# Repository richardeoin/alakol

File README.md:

# _Alakol_

The non-uniform stress / strain accross a balloon's surface is of interest
for superpressure balloon design. Additionally the technique of
"pre-stretching" can be used to modify the balloon's surface stress
distribution.

**Example plot of stress in a mylar balloon shape, before pre-stretching**

However the understanding of this process, especially for the [mylar
balloon][mylar-balloon] shape popular among amateurs for its simplicity,
has not developed much beyond alchemy. At least in part this is due to a
lack of data and repeatable experiments, and difficulties in controlling
external variables given that some experiments last for 10s of hours.

_Alakol_ is a specialised datalogger for collecting data about the
pre-stretching process. It measures:

- **Gauge pressure** the difference in pressure between inside the balloon
  envelope and outside
- **Ambient temperature** using a K-Type thermocouple
- **Absolute ambient pressure** which can be used to remove any effect
  from ambient pressure changing over time
- **Board Temperature** used as the cold-junction temperature for the
  thermocouple and also useful for calibrating the gauge pressure
  measurement against temperature

The _Alakol_ re-uses the mechanical elements from an Omron M2 Blood
Pressure Monitor (BPM). It can pump ambient air into a +ve pressure up to
~40kPa at a (roughly) constant rate, and then release this pressure via a
solenoid controlled valve. This is not the first superpressure balloon
project to re-use the Omron M2 BPM (was this Leo?) but it takes the
additional step of building a datalogger around it.

🚧🚧🚧🚧
WARNING: The Omron M2 Blood Pressure Monitor is a consumer medical device,
but after the modifications described here it is **no longer suitable for
its original purpose** nor should it be used on people (or anything alive
really). Before modifying an Omron M2 you must ensure it is surpless to any
medical requirements, and that it is clearly marked as non-medical. After
modification the original display panel will no longer fit, which ensures
the extent of the modification is abundantly clear to anyone. The Ormon M2
can usually be purchased off the shelf at consumer stores.
🚧🚧🚧🚧🚧

Project Goals:

- Measure all of the obvious enviromental variables.
- Be pleasant to use.

Not a Goal:

- Be very low cost.

### Hardware

The hardware is a 1.6mm thick 4-layer PCB that replaces all of the internal
PCBs in the M2, except from the motor / value breakout PCB (which has no
components anyhow).

The hardware is designed in KiCad. See the [hardware](hardware/) directory.

### Firmware

The firmware runs on a STM32 microcontroller, and is written in Rust. See
the [firmware](firmware/) directory.

A small [OLED display][adafruit-938] displays measurements, and a very
simple user interfaces allows you to cycle between screens, control the
motor and valve, and zero the gauge pressure reading.

Over Ethernet, it offers a HTTP server for commanding the motor and valve,
whilst a separate TCP server on port 8080 streams the measurement data at a
10Hz update rate.

### Data Analysis

There are some python scripts. See the [software](software/) directory.

### License

See each section (hardware/firmware/software).

[mylar-balloon]: https://www.wikipedia.org/wiki/Mylar_balloon_(geometry)
[adafruit-938]: https://www.adafruit.com/product/938

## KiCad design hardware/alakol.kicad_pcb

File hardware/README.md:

# _Alakol_ hardware
## Replacement control board for the Omron M2

---

## Hardware Overview

* Omron 2SMPP-02 gauge pressure sensor
  * Resistive wheatstone bridge
  * TI REF3325 + LTC2064 to provide constant current source
  * AD8226 In-Amp
* MS5607 Sensor
  * Ambient Pressure
  * Board Temperature (close to 2SMPP-02)
* K-Type Thermocouple (Al/Ch)
  * AD8226 In-Amp
* Microcontroller
  * STM32H743VIT6
  * KSZ8081RN Ethernet PHY
* DC Power Jack
  * Centre +ve
  * 4.6V - 18V
  * Or 4xAA batteries!
* Fits in existing Omron M2 housing
  * Dimensions: 78.0mm x 56.0mm (3.07" x 2.20")

| | |
| --- | --- |
| Schematic | [svg](output/schematic/svg/alakol.svg)/[pdf](output/schematic/pdf/alakol.pdf)
| BOM | [csv](output/bom/bom.csv)
| Layout | [svg](output/layout/svg)/[pdf](output/layout/pdf)/[dxf](output/layout/dxf)
| Gerbers | [gerbers](output/layout/gerber)

---

## License

Hardware is licensed under CERN OHL v1.2. See [LICENSE.md](LICENSE.md)

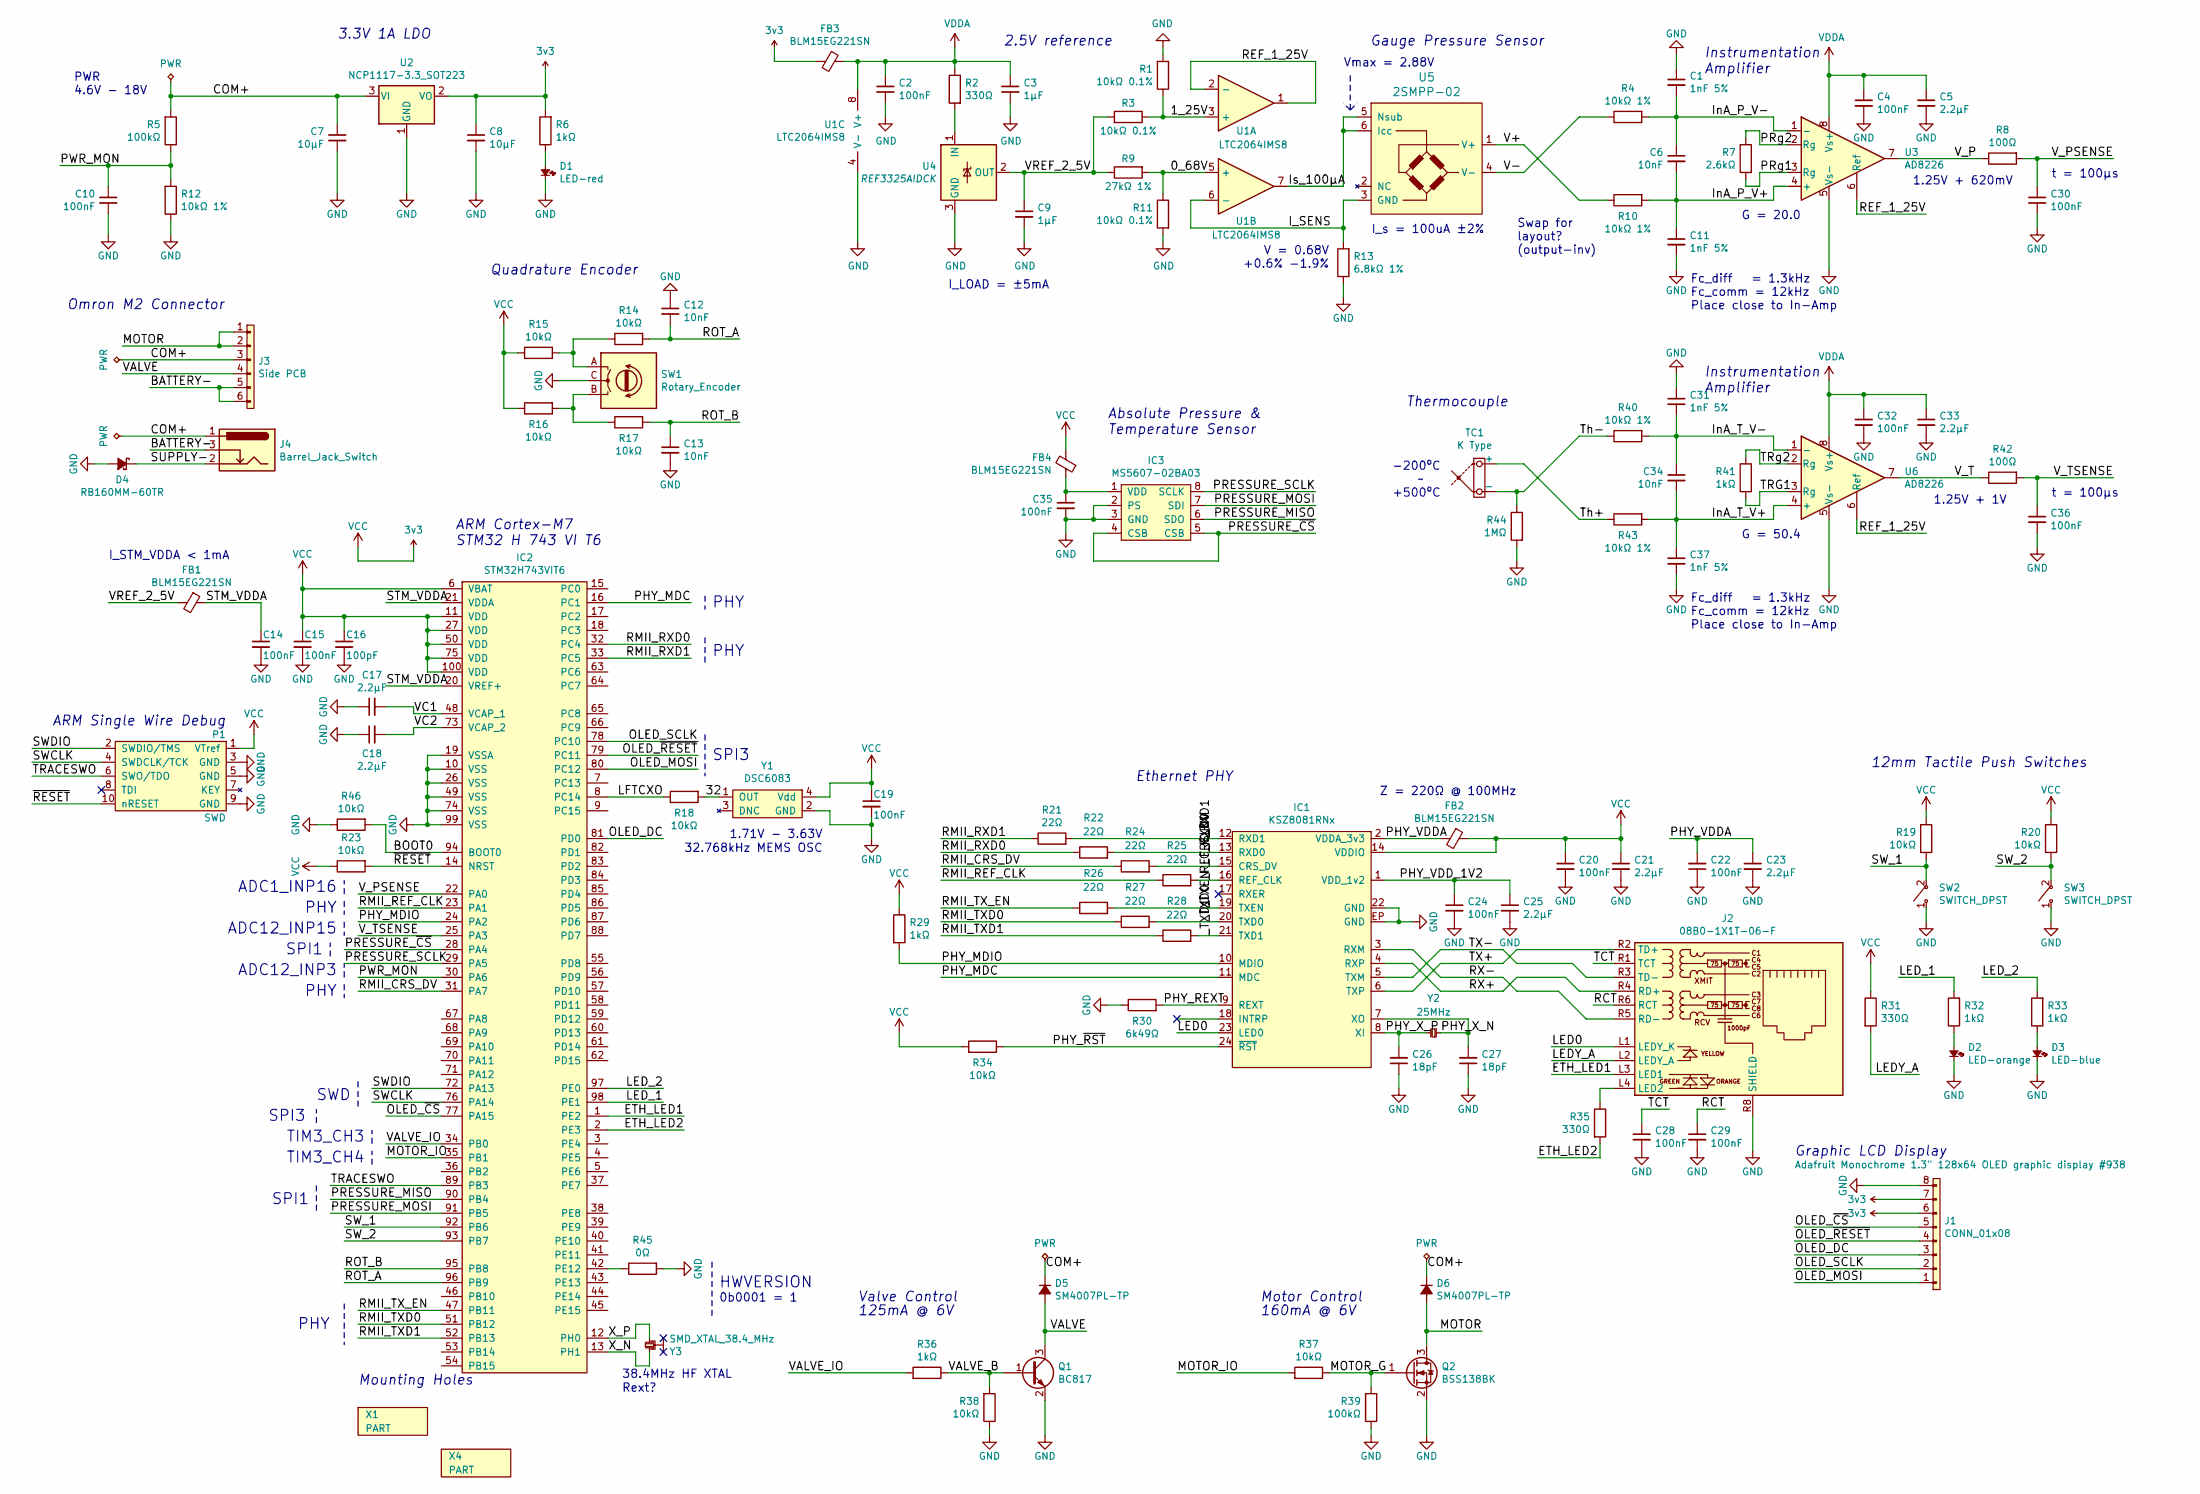
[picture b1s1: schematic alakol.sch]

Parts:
C1, C11, C31, C37: 1nF 5%; 0402
C2, C4, C10, C14, C15, C19, C20, C22, C24, C28, C29, C30, C32, C35, C36: 100nF; 0402
C3, C9: 1µF; 0402
C5, C17, C18, C21, C23, C25, C33: 2.2µF; 0603
C6, C12, C13, C34: 10nF; 0402
C7, C8: 10µF; 0603
C16: 100pF; 0402
C26, C27: 18pF; 0402
D1: LED-red; 0603-LED
D2: LED-orange; 0603-LED
D3: LED-blue; 0603-LED
D4: RB160MM-60TR; D_SOD-123; Farnell 2673070
D5, D6: SM4007PL-TP; D_SOD-123F; Digikey SM4007PL-TPMSCT-ND
FB1, FB2, FB3, FB4: BLM15EG221SN; 0402; Digikey 490-4005-1-ND
IC1: KSZ8081RNx; QFN-24-EP-MICREL; Farnell 2509802
IC2: STM32H743VIT6; LQFP-100; Farnell 2820776
IC3: MS5607-02BA03; MS5611; Digikey 223-1198-1-ND
J1: CONN_01x08; SIL-254P-08; Digikey 1528-1512-ND
J2: 08B0-1X1T-06-F; Digikey 507-1445-ND
J3: Side PCB; Omron_Playbook_Footprint
J4: Barrel_Jack_Switch; BarrelJack_CUI_PJ-102AH_Horizontal
P1: SWD; FTSH-105-01-L-DV-K-ANCHOR; Farnell 2856879
Q1: BC817; SOT-23; Digikey 1727-2919-1-ND
Q2: BSS138BK; SOT-23; Digikey BSS138BK,215
R1, R3, R11: 10kΩ 0.1%; 0402
R2, R31, R35: 330Ω; 0402
R4, R10, R12, R40, R43: 10kΩ 1%; 0402
R5, R39: 100kΩ; 0402
R6, R29, R32, R33, R36, R41: 1kΩ; 0402
R7: 2.6kΩ; 0402
R8, R42: 100Ω; 0402
R9: 27kΩ 1%; 0402
R13: 6.8kΩ 1%; 0402
R14, R15, R16, R17, R18, R19, R20, R23, R34, R37, R38, R46: 10kΩ; 0402
R21, R22, R24, R25, R26, R27, R28: 22Ω; 0402
R30: 6k49Ω; 0402; Farnell 1469727
R44: 1MΩ; 0402
R45: 0Ω; 0402
SW1: Rotary_Encoder; PEC11R-4xxxF-Nxxxx; Digikey PEC11R-4215F-N0024-ND
SW2, SW3: SWITCH_DPST; SW_PUSH-12mm-OMRON_4xxx_5xxx; Part Omron B3F-4000; Digikey SW411-ND
TC1: K Type; PCC-SMP; Digikey 1568-1306-ND
U1: LTC2064IMS8; MSOP-8; Digikey LTC2064IMS8#PBF-ND
U2: NCP1117-3.3_SOT223; SOT-223-3_TabPin2; Digikey NCP1117ST33T3GOSCT-ND
U3, U6: AD8226; MSOP-8; Digikey AD8226ARMZ-ND
U4: REF3325AIDCK; SOT-323; Digikey 296-39164-1-ND
U5: 2SMPP-02; Farnell 2113270
X1, X4: PART; drill
Y1: DSC6083; XTAL-32x25-CDFN4; Digikey DSC6083CI2A-032K768-ND
Y2: 25MHz; XTAL-50x32; Digikey 535-10645-1-ND
Y3: SMD_XTAL_38.4_MHz; XTAL-25x20; Farnell 2849405

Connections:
3v3: C8.1, C15.1, C16.1, C19.1, C20.1, C21.1, FB2.1, FB3.2, FB4.2, IC1.14 (VDDIO), IC2.6 (VBAT), IC2.11 (VDD), IC2.27 (VDD), IC2.50 (VDD), IC2.75 (VDD), IC2.100 (VDD), J1.6, J1.7, P1.1 (VTref), R6.2, R15.1, R16.1, R19.2, R20.2, R23.1, R29.1, R31.1, R34.2, U2.2 (VO), Y1.4 (Vdd)
/0_68V: R9.2, R11.1, U1.5 (+)
/1_25V: R1.1, R3.1, U1.3 (+)
/32: R18.2, Y1.1 (OUT)
/BATTERY-: J3.5, J3.6, J4.3
/BOOT0: IC2.94 (BOOT0), R46.2
/COM+: C7.1, D5.1 (K), D6.1 (K), J3.3, J4.1, R5.2, U2.3 (VI)
/ETH_LED1: IC2.1 (PE2), J2.L3 (LED1)
/ETH_LED2: IC2.2 (PE3), R35.2
/I_SENS: R13.2, U1.6 (-), U5.3 (GND)
/InA_P_V+: C6.2, C11.1, R10.2, U3.4 (+)
/InA_P_V-: C1.2, C6.1, R4.2, U3.1 (-)
/InA_T_V+: C34.2, C37.1, R43.2, U6.4 (+)
/InA_T_V-: C31.2, C34.1, R40.2, U6.1 (-)
/Is_100µA: U1.7, U5.5 (Nsub), U5.6 (Icc)
/LED0: IC1.23 (LED0), J2.L1 (LEDY_K)
/LEDY_A: J2.L2 (LEDY_A), R31.2
/LED_1: IC2.98 (PE1), R32.2
/LED_2: IC2.97 (PE0), R33.2
/LFTCXO: IC2.8 (PC14), R18.1
/MOTOR: D6.2 (A), J3.1, J3.2, Q2.3 (D)
/MOTOR_G: Q2.1 (G), R37.1, R39.2
/MOTOR_IO: IC2.35 (PB1), R37.2
/OLED_DC: IC2.81 (PD0), J1.3
/OLED_MOSI: IC2.80 (PC12), J1.1
/OLED_SCLK: IC2.78 (PC10), J1.2
/OLED_~CS~: IC2.77 (PA15), J1.5
/OLED_~RESET~: IC2.79 (PC11), J1.4
/PHY_MDC: IC1.11 (MDC), IC2.16 (PC1)
/PHY_MDIO: IC1.10 (MDIO), IC2.24 (PA2), R29.2
/PHY_REXT: IC1.9 (REXT), R30.2
/PHY_VDDA: C22.2, C23.1, FB2.2, IC1.2 (VDDA_3v3)
/PHY_VDD_1V2: C24.1, C25.1, IC1.1 (VDD_1v2)
/PHY_X_N: C27.2, IC1.7 (XO), Y2.1
/PHY_X_P: C26.2, IC1.8 (XI), Y2.2
/PHY_~RST~: IC1.24 (~RST), R34.1
/PRESSURE_MISO: IC2.90 (PB4), IC3.6 (SDO)
/PRESSURE_MOSI: IC2.91 (PB5), IC3.7 (SDI)
/PRESSURE_SCLK: IC2.29 (PA5), IC3.8 (SCLK)
/PRESSURE_~CS~: IC2.28 (PA4), IC3.4 (CSB), IC3.5 (CSB)
/PRg1: R7.2, U3.3 (Rg)
/PRg2: R7.1, U3.2 (Rg)
/PWR_MON: C10.1, IC2.30 (PA6), R5.1, R12.2
/RCT: C29.1, J2.R6 (RCT)
/REF_1_25V: U1.1, U1.2 (-), U3.6 (Ref), U6.6 (Ref)
/RMII_CRS_DV: IC2.31 (PA7), R24.1
/RMII_REF_CLK: IC2.23 (PA1), R25.1
/RMII_RXD0: IC2.32 (PC4), R22.1
/RMII_RXD1: IC2.33 (PC5), R21.1
/RMII_TXD0: IC2.51 (PB12), R27.1
/RMII_TXD1: IC2.52 (PB13), R28.1
/RMII_TX_EN: IC2.47 (PB11), R26.1
/ROT_A: C12.2, IC2.96 (PB9), R14.2
/ROT_B: C13.1, IC2.95 (PB8), R17.2
/RX+: IC1.4 (RXP), J2.R4 (RD+)
/RX-: IC1.3 (RXM), J2.R5 (RD-)
/STM_VDDA: C14.1, FB1.1, IC2.20 (VREF+), IC2.21 (VDDA)
/SUPPLY-: D4.1 (K), J4.2
/SWCLK: IC2.76 (PA14), P1.4 (SWDCLK/TCK)
/SWDIO: IC2.72 (PA13), P1.2 (SWDIO/TMS)
/SW_1: IC2.92 (PB6), R19.1, SW2.2
/SW_2: IC2.93 (PB7), R20.1, SW3.2
/TCT: C28.1, J2.R1 (TCT)
/TRACESWO: IC2.89 (PB3), P1.6 (SWO/TDO)
/TRG1: R41.2, U6.3 (Rg)
/TRg2: R41.1, U6.2 (Rg)
/TX+: IC1.6 (TXP), J2.R2 (TD+)
/TX-: IC1.5 (TXM), J2.R3 (TD-)
/Th+: R43.1, TC1.1 (+)
/Th-: R40.1, R44.1, TC1.2 (-)
/V+: R10.1, U5.1 (V+)
/V-: R4.1, U5.4 (V-)
/VALVE: D5.2 (A), J3.4, Q1.3 (C)
/VALVE_B: Q1.1 (B), R36.1, R38.2
/VALVE_IO: IC2.34 (PB0), R36.2
/VC1: C17.2, IC2.48 (VCAP_1)
/VC2: C18.2, IC2.73 (VCAP_2)
/VREF_2_5V: C9.1, FB1.2, R3.2, R9.1, U4.2 (OUT)
/V_P: R8.1, U3.7
/V_PSENSE: C30.1, IC2.22 (PA0), R8.2
/V_T: R42.1, U6.7
/V_TSENSE: C36.1, IC2.25 (PA3), R42.2
/X_N: IC2.13 (PH1), Y3.3
/X_P: IC2.12 (PH0), Y3.1
/_CRS_DV: IC1.15 (CRS_DV), R24.2
/_REF_CLK: IC1.16 (REF_CLK), R25.2
/_RXD0: IC1.13 (RXD0), R22.2
/_RXD1: IC1.12 (RXD1), R21.2
/_TXD0: IC1.20 (TXD0), R27.2
/_TXD1: IC1.21 (TXD1), R28.2
/_TXEN: IC1.19 (TXEN), R26.2
/~RESET: IC2.14 (NRST), P1.10 (nRESET), R23.2
GND: C1.1, C2.2, C3.2, C4.2, C5.2, C7.2, C8.2, C9.2, C10.2, C11.2, C12.1, C13.2, C14.2, C15.2, C16.2, C17.1, C18.1, C19.2, C20.2, C21.2, C22.1, C23.2, C24.2, C25.2, C26.1, C27.1, C28.2, C29.2, C30.2, C31.1, C32.2, C33.2, C35.2, C36.2, C37.2, D1.1, D2.1, D3.1, D4.2 (A), IC1.22 (GND), IC1.EP (GND), IC2.10 (VSS), IC2.19 (VSSA), IC2.26 (VSS), IC2.49 (VSS), IC2.74 (VSS), IC2.99 (VSS), IC3.2 (PS), IC3.3 (GND), J1.8, J2.R8 (SHIELD), P1.3 (GND), P1.5 (GND), P1.9 (GND), Q1.2 (E), Q2.2 (S), R1.2, R11.2, R12.1, R13.1, R30.1, R38.1, R39.1, R44.2, R45.2, R46.1, SW1.C, SW2.1, SW3.1, U1.4 (V-), U2.1 (GND), U3.5 (Vs-), U4.3 (GND), U6.5 (Vs-), Y1.2 (GND)
unnamed: C35.1, FB4.1, IC3.1 (VDD)
unnamed: D1.2, R6.1
unnamed: D2.2, R32.1
unnamed: D3.2, R33.1
unnamed: IC2.42 (PE12), R45.1
unnamed: J2.L4 (LED2), R35.1
unnamed: R2.2, U4.1 (IN)
unnamed: R14.1, R15.2, SW1.A
unnamed: R16.2, R17.1, SW1.B
VDDA: C2.1, C3.1, C4.1, C5.1, C32.1, C33.1, FB3.1, R2.1, U1.8 (V+), U3.8 (Vs+), U6.8 (Vs+)

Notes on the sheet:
ARM Cortex-M7 STM32 H 743 VI T6
ARM Single Wire Debug
38.4MHz HF XTAL
1.71V - 3.63V
Graphic LCD Display
Mounting Holes
32.768kHz MEMS OSC
3.3V 1A LDO
12mm Tactile Push Switches
PWR 4.6V - 18V
Quadrature Encoder
Rext?
PHY
SWD
Ethernet PHY
Gauge Pressure Sensor
G = 20.0
Fc_diff = 1.3kHz Fc_comm = 12kHz Place close to In-Amp
I_s = 100uA ±2%
Instrumentation Amplifier
2.5V reference
1.25V + 620mV
Swap for layout? (output-inv)
Z = 220Ω @ 100MHz
I_STM_VDDA < 1mA
Vmax = 2.88V
V = 0.68V +0.6% -1.9%
Omron M2 Connector
Valve Control
Motor Control
G = 50.4
1.25V + 1V
-200ºC ~~ +500ºC
I_LOAD = ±5mA
t = 100µs
Absolute Pressure & Temperature Sensor
Thermocouple
125mA @ 6V
160mA @ 6V
SPI3

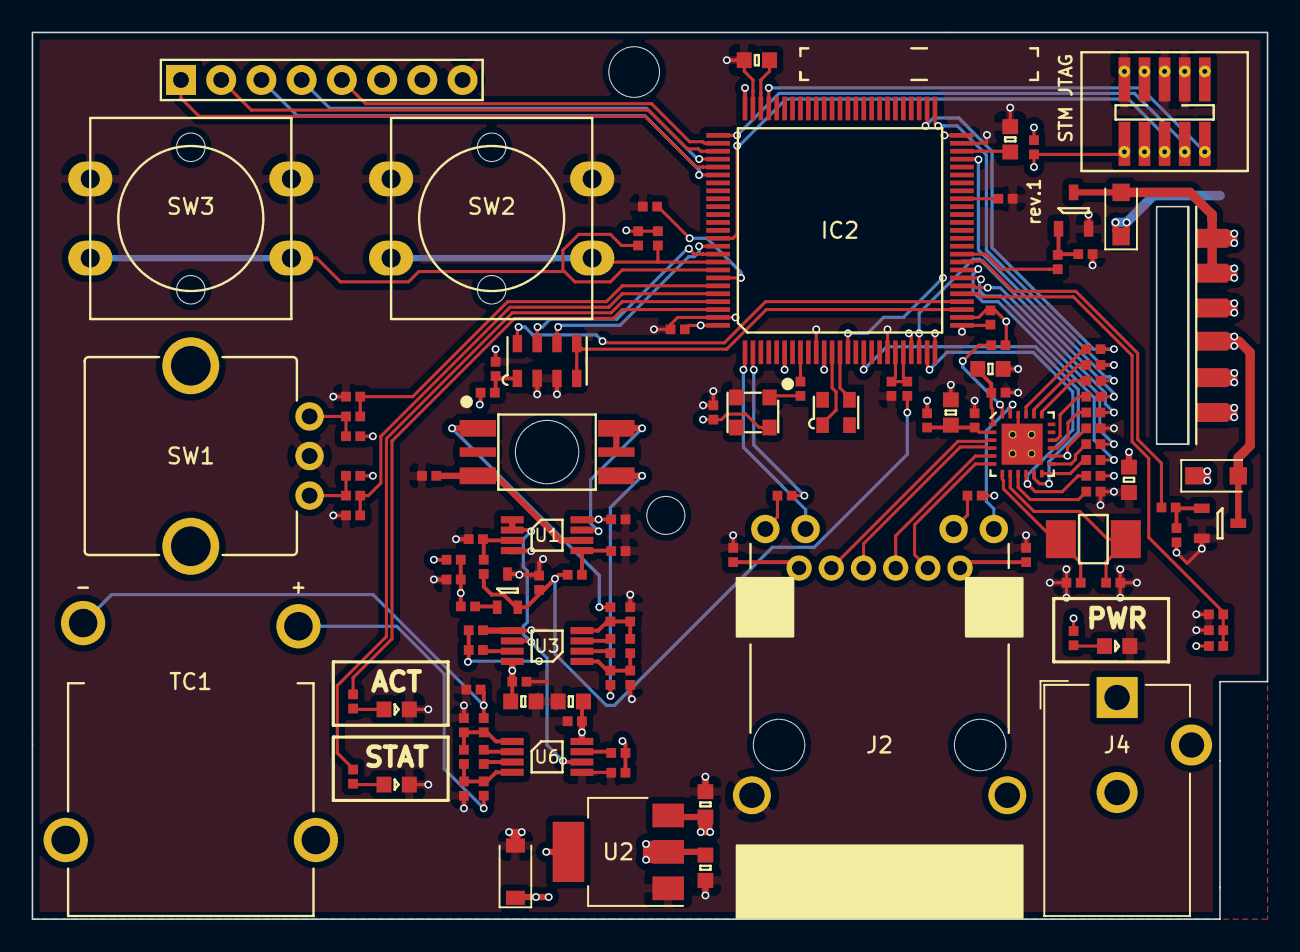
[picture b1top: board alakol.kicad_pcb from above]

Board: 4 copper layers, 78.0 x 56.0 mm, 118 parts (0 on the bottom side), 103 nets.

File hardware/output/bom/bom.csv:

Reference, Quantity, Value, Footprint, Datasheet, Digikey, Farnell, Toby, Module, THT, Part, User Manual
C11 C1 C37 C31 ,4,"1nF 5%","agg:0402",""
C12 C13 C6 C34 ,4,"10nF","agg:0402",""
C15 C10 C19 C24 C20 C22 C28 C29 C4 C2 C14 C32 C36 C30 C35 ,15,"100nF","agg:0402",""
C16 ,1,"100pF","agg:0402",""
C17 C18 C25 C21 C5 C23 C33 ,7,"2.2µF","agg:0603",""
C27 C26 ,2,"18pF","agg:0402",""
C3 C9 ,2,"1µF","agg:0402",""
C8 C7 ,2,"10µF","agg:0603",""
D1 ,1,"LED-red","agg:0603-LED",""
D2 ,1,"LED-orange","agg:0603-LED",""
D3 ,1,"LED-blue","agg:0603-LED",""
D4 ,1,"RB160MM-60TR","Diode_SMD:D_SOD-123","https://www.rohm.com/datasheet/RB160MM-60/rb160mm-60tr-e","","2673070","","","","",""
D5 D6 ,2,"SM4007PL-TP","Diode_SMD:D_SOD-123F","http://www.mccsemi.com/up_pdf/SM4001PL-SM4007PL(SOD-123FL).PDF","SM4007PL-TPMSCT-ND","2295709","","","","",""
FB2 FB1 FB3 FB4 ,4,"BLM15EG221SN","agg:0402","https://www.murata.com/en-us/products/productdata/8796750970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","490-4005-1-ND","","","","","",""
IC1 ,1,"KSZ8081RNx","agg:QFN-24-EP-MICREL","http://ww1.microchip.com/downloads/en/DeviceDoc/KSZ8081RNA_RND.pdf","","2509802","","","","",""
IC2 ,1,"STM32H743VIT6","agg:LQFP-100","http://www.st.com/st-web-ui/static/active/en/resource/techni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","497-17720-ND","2820776","","","","",""
IC3 ,1,"MS5607-02BA03","agg:MS5611","https://www.te.com/commerce/DocumentDelivery/DDEController?A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","223-1198-1-ND","","","","","",""
J1 ,1,"CONN_01x08","agg:SIL-254P-08","","1528-1512-ND","","","Adafruit Monochrome 1.3" 128x64 OLED graphic display #938","true","",""
J2 ,1,"08B0-1X1T-06-F","rem:08B0-1X1T-06-F","https://www.belfuse.com/resources/ICMs/ICMs%20Drawings/08B0-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","507-1445-ND","2675992","","","true","",""
J3 ,1,"Side PCB","rem:Omron_Playbook_Footprint","","","","","","true","",""
J4 ,1,"Barrel_Jack_Switch","Connector_BarrelJack:BarrelJack_CUI_PJ-102AH_Horizontal","https://www.cui.com/product/resource/pj-102ah.pdf","","","","","true","",""
P1 ,1,"SWD","rem:FTSH-105-01-L-DV-K-ANCHOR","","SAM13165CT-ND","2856879","FTSH-105-01-L-DV-K","","","",""
Q1 ,1,"BC817","agg:SOT-23","https://assets.nexperia.com/documents/data-sheet/BC817_SER.pdf","1727-2919-1-ND","","","","","",""
Q2 ,1,"BSS138BK","agg:SOT-23","https://assets.nexperia.com/documents/data-sheet/BSS138BK.pdf","BSS138BK,215","","","","","",""
R11 R3 R1 ,3,"10kΩ 0.1%","agg:0402",""
R12 R4 R10 R40 R43 ,5,"10kΩ 1%","agg:0402",""
R13 ,1,"6.8kΩ 1%","agg:0402",""
R23 R18 R19 R20 R15 R16 R17 R14 R34 R38 R37 R46 ,12,"10kΩ","agg:0402",""
R28 R27 R26 R25 R24 R22 R21 ,7,"22Ω","agg:0402",""
R30 ,1,"6k49Ω","agg:0402","","","1469727","","","","",""
R31 R35 R2 ,3,"330Ω","agg:0402",""
R36 R6 R33 R32 R29 R41 ,6,"1kΩ","agg:0402",""
R44 ,1,"1MΩ","agg:0402",""
R45 ,1,"0Ω","agg:0402",""
R5 R39 ,2,"100kΩ","agg:0402",""
R7 ,1,"2.6kΩ","agg:0402",""
R8 R42 ,2,"100Ω","agg:0402",""
R9 ,1,"27kΩ 1%","agg:0402",""
SW1 ,1,"Rotary_Encoder","rem:PEC11R-4xxxF-Nxxxx","https://www.bourns.com/docs/Product-Datasheets/PEC11R.pdf","PEC11R-4215F-N0024-ND","","","","true","",""
SW2 SW3 ,2,"SWITCH_DPST","rem:SW_PUSH-12mm-OMRON_4xxx_5xxx","https://omronfs.omron.com/en_US/ecb/products/pdf/en-b3f.pdf","SW411-ND","","","","true","Omron B3F-4000",""
TC1 ,1,"K Type","rem:PCC-SMP","https://cdn.sparkfun.com/datasheets/Prototyping/PCC-SMP-K-da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","1568-1306-ND","","","","true","",""
U1 ,1,"LTC2064IMS8","agg:MSOP-8","https://www.analog.com/media/en/technical-documentation/data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","LTC2064IMS8#PBF-ND","","","","","",""
U2 ,1,"NCP1117-3.3_SOT223","Package_TO_SOT_SMD:SOT-223-3_TabPin2","http://www.onsemi.com/pub_link/Collateral/NCP1117-D.PDF","NCP1117ST33T3GOSCT-ND","","","","","",""
U3 U6 ,2,"AD8226","agg:MSOP-8","https://www.analog.com/media/en/technical-documentation/data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","AD8226ARMZ-ND","","","","","",""
U4 ,1,"REF3325AIDCK","agg:SOT-323","http://www.ti.com/lit/ds/symlink/ref3325.pdf","296-39164-1-ND","","","","","",""
U5 ,1,"2SMPP-02","rem:2SMPP-02","https://omronfs.omron.com/en_US/ecb/products/pdf/en-2smpp-02.pdf","Z3059-ND","2113270","","","","","https://omronfs.omron.com/en_US/ecb/products/pdf/en_a282_e1_01.pdf"
X1 X4 ,2,"PART","rem:drill",""
Y1 ,1,"DSC6083","rem:XTAL-32x25-CDFN4","http://ww1.microchip.com/downloads/en/DeviceDoc/DSC60XX-Ultr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","DSC6083CI2A-032K768-ND","","","","","",""
Y2 ,1,"25MHz","agg:XTAL-50x32","https://abracon.com/Resonators/abm3.pdf","535-10645-1-ND","2101328","","","","",""
Y3 ,1,"SMD_XTAL_38.4_MHz","agg:XTAL-25x20","http://www.farnell.com/datasheets/2581416.pdf","535-13191-1-ND","2849405","","","","",""

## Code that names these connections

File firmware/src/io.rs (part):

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
#[cfg(feature = "hardware0")]
pub type PressureSPIPinsT = (
    gpio::gpiob::PB3<Alternate<AF5>>,
    gpio::gpiob::PB4<Alternate<AF5>>,
    gpio::gpiob::PB5<Alternate<AF5>>,
);
#[cfg(not(feature = "hardware0"))]
pub type PressureSPIPinsT = (
    gpio::gpioa::PA5<Alternate<AF5>>,
    gpio::gpiob::PB4<Alternate<AF5>>,
    gpio::gpiob::PB5<Alternate<AF5>>,
);

pub fn gpio_setup(
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    u8,
    (
        // ethernet led
        gpio::gpioe::PE2<Output<PushPull>>,
        gpio::gpioe::PE3<Output<PushPull>>,
    ),
    gpio::gpioe::PE0<Output<PushPull>>, // stat_led
    gpio::gpioe::PE1<Output<PushPull>>, // act_led
    (
        // oled
        gpio::gpioc::PC10<Alternate<AF6>>,
        spi::NoMiso,
        gpio::gpioc::PC12<Alternate<AF6>>,
    ),
    gpio::gpiod::PD0<Output<PushPull>>,
    gpio::gpioc::PC11<Output<PushPull>>,
    gpio::gpioa::PA15<Output<PushPull>>,
    PressureSPIPinsT,
    gpio::gpioa::PA4<Output<PushPull>>, // pressure_cs
    gpio::gpioa::PA0<Analog>,
    gpio::gpioa::PA3<Analog>,
    gpio::gpioa::PA6<Analog>,
    gpio::gpiob::PB0<Output<PushPull>>, // valve_io
    gpio::gpiob::PB1<Alternate<AF2>>,   // motor_io
) {
    // Hardware version
    let h0 = gpioe.pe12.into_pull_up_input();
    let h1 = gpioe.pe13.into_pull_up_input();
    let h2 = gpioe.pe14.into_pull_up_input();
    let h3 = gpioe.pe15.into_pull_up_input();
    let hw = hardware_version(h0, h1, h2, h3).expect("Unknown version");

    // Stat LED
    let stat_led = gpioe.pe0.into_push_pull_output();
    // Act LED
    let act_led = gpioe.pe1.into_push_pull_output();

    // Ethernet LED
    let ethernet_led = (
        gpioe.pe2.into_push_pull_output(),
        gpioe.pe3.into_push_pull_output(),
    );

    // SW
    gpiob.pb6.into_pull_up_input();
    gpiob.pb7.into_pull_up_input();
    gpiob.pb8.into_pull_up_input();
    gpiob.pb9.into_pull_up_input();
    debounce_tick(true);

    // PB3 TRACESWO
    #[cfg(not(feature = "hardware0"))]
    let _traceswo = gpiob.pb3.into_alternate_af0().set_speed(Speed::VeryHigh);

    // Ethernet
    let rmii_ref_clk = gpioa.pa1.into_alternate_af11();
    rmii_ref_clk.set_speed(Speed::VeryHigh);
    let rmii_mdio = gpioa.pa2.into_alternate_af11();
    rmii_mdio.set_speed(Speed::VeryHigh);
    let rmii_mdc = gpioc.pc1.into_alternate_af11();
    rmii_mdc.set_speed(Speed::VeryHigh);
    let rmii_crs_dv = gpioa.pa7.into_alternate_af11();
    rmii_crs_dv.set_speed(Speed::VeryHigh);
    let rmii_rxd0 = gpioc.pc4.into_alternate_af11();
    rmii_rxd0.set_speed(Speed::VeryHigh);
    let rmii_rxd1 = gpioc.pc5.into_alternate_af11();
    rmii_rxd1.set_speed(Speed::VeryHigh);
    let rmii_tx_en = gpiob.pb11.into_alternate_af11();
    rmii_tx_en.set_speed(Speed::VeryHigh);
    let rxii_txd0 = gpiob.pb12.into_alternate_af11();
    rxii_txd0.set_speed(Speed::VeryHigh);
    let rmii_txd1 = gpiob.pb13.into_alternate_af11();
    rmii_txd1.set_speed(Speed::VeryHigh);

    // OLED
    let oled_sck = gpioc.pc10.into_alternate_af6();
    let oled_miso = spi::NoMiso;
    let oled_mosi = gpioc.pc12.into_alternate_af6();
    let oled_spi = (oled_sck, oled_miso, oled_mosi);
    let oled_dc = gpiod.pd0.into_push_pull_output();
    let oled_rst = gpioc.pc11.into_push_pull_output();
    let oled_cs = gpioa.pa15.into_push_pull_output();

    // Pressure sensor
    #[cfg(feature = "hardware0")]
    let pressure_sck = gpiob.pb3.into_alternate_af5();
    #[cfg(not(feature = "hardware0"))]
    let pressure_sck = gpioa.pa5.into_alternate_af5();
    let pressure_miso = gpiob.pb4.into_alternate_af5();
    let pressure_mosi = gpiob.pb5.into_alternate_af5();
    let pressure_spi = (pressure_sck, pressure_miso, pressure_mosi);
    let pressure_cs = gpioa.pa4.into_push_pull_output();

    // ADCs
    let v_psense = gpioa.pa0.into_analog();
    let v_tsense = gpioa.pa3.into_analog();
    let pwr_mon = gpioa.pa6.into_analog();

    // Motors
    let valve_io = gpiob.pb0.into_push_pull_output();
    let motor_io = gpiob.pb1.into_alternate_af2();

    // Hardware
    (
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}

pub fn hardware_version(
    h0: gpio::gpioe::PE12<Input<PullUp>>,
    h1: gpio::gpioe::PE13<Input<PullUp>>,
    h2: gpio::gpioe::PE14<Input<PullUp>>,
    h3: gpio::gpioe::PE15<Input<PullUp>>,
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/// Set state of ethernet LED
pub fn ethernet_led(
    ethernet_led: &mut (
        gpio::gpioe::PE2<Output<PushPull>>,
        gpio::gpioe::PE3<Output<PushPull>>,
    ),
    state: EthernetLED,
) -> Result<(), Never> {
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
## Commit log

2020-04-18 stm32-based hardware for fabriation, rev.0
2020-04-18 Add firmware
2020-04-18 Hardware rev.1
2020-04-18 Add software, with examples and README
2020-04-18 Write a README for the whole project
2020-04-18 Add travis
2020-04-18 Tidy up unused git modules, fix markdown
2020-04-18 Let autoformatter loose on python code
    I don't want to think about formatting
2020-04-18 Add photos, add README for hardware
2020-04-19 Fix units for ms5611 pressure
2020-04-19 Improve READMEs for firmware and software
2020-04-19 Tidy gauge pressure format specifier
2020-04-20 Update photo
2020-04-27 Blank display after 1 hour - it fades after 1000 hours
    See note on Adafruit product page https://www.adafruit.com/product/938
    Switch to representing time with a i64 to avoid the 50 day problem,
    involves some unafe but race is not critical anyhow. And rollover probably
    wasn't an issue either
2020-04-27 Add version and git commit hash to display
2020-04-27 Reduce cold junction temperature offset - needs more investigation
2020-06-23 Bump some dependency versions
2020-11-18 Bump notebook from 6.0.3 to 6.1.5 in /software
    Bumps [notebook](https://github.com/jupyter/jupyterhub) from 6.0.3 to 6.1.5.
    - [Release notes](https://github.com/jupyter/jupyterhub/releases)
    - [Changelog](https://github.com/jupyterhub/jupyterhub/blob/master/CHECKLIST-Release.md)
    - [Commits](https://github.com/jupyter/jupyterhub/commits)
2021-02-02 Bump bleach from 3.1.4 to 3.3.0 in /software
    Bumps [bleach](https://github.com/mozilla/bleach) from 3.1.4 to 3.3.0.
    - [Release notes](https://github.com/mozilla/bleach/releases)
    - [Changelog](https://github.com/mozilla/bleach/blob/master/CHANGES)
    - [Commits](https://github.com/mozilla/bleach/compare/v3.1.4...v3.3.0)
2021-03-20 Bump jinja2 from 2.11.1 to 2.11.3 in /software
    Bumps [jinja2](https://github.com/pallets/jinja) from 2.11.1 to 2.11.3.
    - [Release notes](https://github.com/pallets/jinja/releases)
    - [Changelog](https://github.com/pallets/jinja/blob/master/CHANGES.rst)
    - [Commits](https://github.com/pallets/jinja/compare/2.11.1...2.11.3)
2021-03-29 Bump pygments from 2.6.1 to 2.7.4 in /software
    Bumps [pygments](https://github.com/pygments/pygments) from 2.6.1 to 2.7.4.
    - [Release notes](https://github.com/pygments/pygments/releases)
    - [Changelog](https://github.com/pygments/pygments/blob/master/CHANGES)
    - [Commits](https://github.com/pygments/pygments/compare/2.6.1...2.7.4)
2021-06-02 Bump urllib3 from 1.25.8 to 1.26.5 in /software
    Bumps [urllib3](https://github.com/urllib3/urllib3) from 1.25.8 to 1.26.5.
    - [Release notes](https://github.com/urllib3/urllib3/releases)
    - [Changelog](https://github.com/urllib3/urllib3/blob/main/CHANGES.rst)
    - [Commits](https://github.com/urllib3/urllib3/compare/1.25.8...1.26.5)
    ---
    updated-dependencies:
2021-08-23 Bump notebook from 6.0.3 to 6.4.1 in /software
    Bumps [notebook](https://github.com/jupyter/jupyterhub) from 6.0.3 to 6.4.1.
    - [Release notes](https://github.com/jupyter/jupyterhub/releases)
    - [Changelog](https://github.com/jupyterhub/jupyterhub/blob/main/CHECKLIST-Release.md)
    - [Commits](https://github.com/jupyter/jupyterhub/commits)
    ---
    updated-dependencies:
2022-01-21 Bump ipython from 7.13.0 to 7.16.3 in /software
    Bumps [ipython](https://github.com/ipython/ipython) from 7.13.0 to 7.16.3.
    - [Release notes](https://github.com/ipython/ipython/releases)
    - [Commits](https://github.com/ipython/ipython/compare/7.13.0...7.16.3)
    ---
    updated-dependencies:
    - dependency-name: ipython
2022-04-06 Bump notebook from 6.0.3 to 6.4.10 in /software
    Bumps [notebook](http://jupyter.org) from 6.0.3 to 6.4.10.
    ---
    updated-dependencies:
    - dependency-name: notebook
    dependency-type: direct:production
    ...
2022-06-16 Bump notebook from 6.0.3 to 6.4.12 in /software
    Bumps [notebook](http://jupyter.org) from 6.0.3 to 6.4.12.
    ---
    updated-dependencies:
    - dependency-name: notebook
    dependency-type: direct:production
    ...
2022-06-22 Bump numpy from 1.18.2 to 1.22.0 in /software
    Bumps [numpy](https://github.com/numpy/numpy) from 1.18.2 to 1.22.0.
    - [Release notes](https://github.com/numpy/numpy/releases)
    - [Changelog](https://github.com/numpy/numpy/blob/main/doc/HOWTO_RELEASE.rst)
    - [Commits](https://github.com/numpy/numpy/compare/v1.18.2...v1.22.0)
    ---
    updated-dependencies:
2022-07-29 Bump mistune from 0.8.4 to 2.0.3 in /software
    Bumps [mistune](https://github.com/lepture/mistune) from 0.8.4 to 2.0.3.
    - [Release notes](https://github.com/lepture/mistune/releases)
    - [Changelog](https://github.com/lepture/mistune/blob/master/docs/changes.rst)
    - [Commits](https://github.com/lepture/mistune/compare/v0.8.4...v2.0.3)
    ---
    updated-dependencies:
2022-08-10 Bump nbconvert from 5.6.1 to 6.3.0 in /software
    Bumps [nbconvert](https://github.com/jupyter/nbconvert) from 5.6.1 to 6.3.0.
    - [Release notes](https://github.com/jupyter/nbconvert/releases)
    - [Commits](https://github.com/jupyter/nbconvert/compare/5.6.1...6.3.0)
    ---
    updated-dependencies:
    - dependency-name: nbconvert
2022-08-23 Bump nbconvert from 5.6.1 to 6.5.1 in /software
    Bumps [nbconvert](https://github.com/jupyter/nbconvert) from 5.6.1 to 6.5.1.
    - [Release notes](https://github.com/jupyter/nbconvert/releases)
    - [Commits](https://github.com/jupyter/nbconvert/compare/5.6.1...6.5.1)
    ---
    updated-dependencies:
    - dependency-name: nbconvert
2022-12-08 Bump certifi from 2019.11.28 to 2022.12.7 in /software
    Bumps [certifi](https://github.com/certifi/python-certifi) from 2019.11.28 to 2022.12.7.
    - [Release notes](https://github.com/certifi/python-certifi/releases)
    - [Commits](https://github.com/certifi/python-certifi/compare/2019.11.28...2022.12.07)
    ---
    updated-dependencies:
    - dependency-name: certifi
